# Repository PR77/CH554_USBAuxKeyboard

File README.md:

# CH554 AUX KEYBOARD INTERFACE
USB MACRO PAD (AUX Keyboard Interface) based on the WCH554 MCS51 based chip with USB Device + Host Interface. 

# Warning
This design has not been compliance tested and will not be. It may cause personal damage to you or others. I take no responsibility for this. I accept no responsibility for any damage to any equipment that results from the use of this design and its components. IT IS ENTIRELY AT YOUR OWN RISK!

# Overview
This project is essentially an open source macro pad which emulates a USB Keyboard, Mouse and Comsumer Device. Additionally, there is an OUT USB end point supported to allow for HOST communication back to the device. My target is to make this easily configurable so different functions can be added to the Rotary Encoder, Push Buttons and OLED display. I'm using this project as an opportunity to learn more about the WCH55x micro controller.

# Appearance Final PCB Version
PCB version has been routed manufactured and tested. Gerbers and design now available as it works as expected. Here is the usual 3D artwork of the design.

# Credits
I refacted a lot of the original libraries into various software components. However there were some repos which provided me with excellent information, tools and resources;
- https://github.com/wagiminator
- https://github.com/Blinkinlabs/ch554_sdcc
- https://github.com/HonghongLu/CH554
- https://github.com/pkourany/clickButton

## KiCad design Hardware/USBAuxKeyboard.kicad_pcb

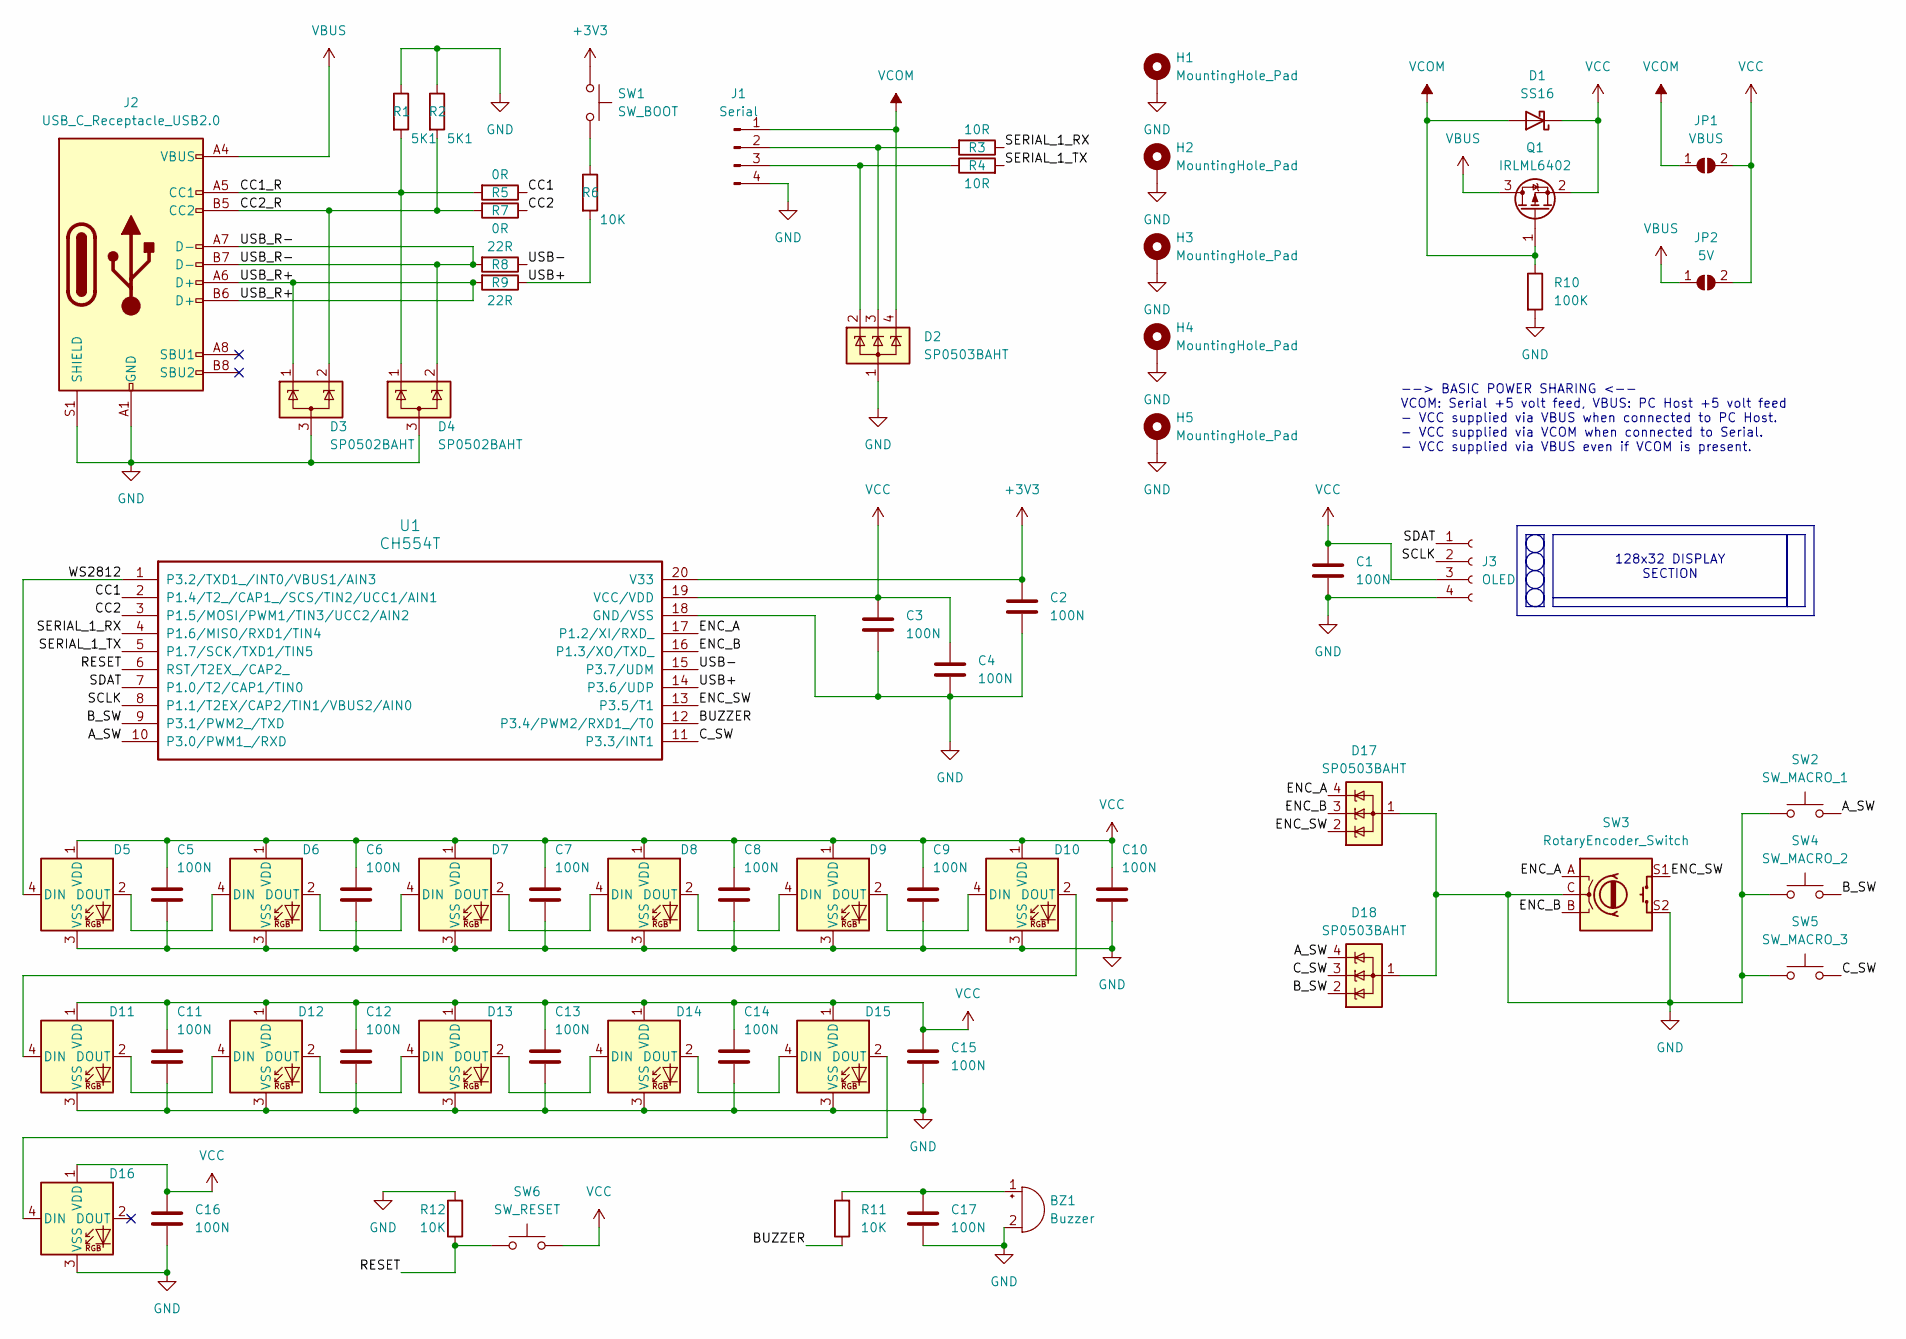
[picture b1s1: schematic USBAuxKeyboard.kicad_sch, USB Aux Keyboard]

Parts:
BZ1: Buzzer; Buzzer_15x7.5RM7.6
C1, C2, C3, C4, C5, C6, C7, C8, C9, C10, C11, C12, C13, C14, C15, C16, C17: 100N; C_0805_2012Metric_Pad1.18x1.45mm_HandSolder
D1: SS16; D_SMA
D2, D17, D18: SP0503BAHT; SOT-143
D3, D4: SP0502BAHT; SOT-23
D5, D6, D7, D8, D9, D10, D11, D12, D13, D14, D15, D16: WS2812B; LED_WS2812B_PLCC4_5.0x5.0mm_P3.2mm
H1, H2, H3, H4, H5: MountingHole_Pad; MountingHole_2.2mm_M2_Pad_Via
J1: Serial; PinHeader_1x04_P2.54mm_Vertical
J2: USB_C_Receptacle_USB2.0; USB_C_Receptacle_HCTL_HC-TYPE-C-16P-01A
J3: OLED; PinSocket_1x04_P2.54mm_Vertical
JP1: VBUS; SolderJumper-2_P1.3mm_Open_RoundedPad1.0x1.5mm
JP2: 5V; SolderJumper-2_P1.3mm_Open_RoundedPad1.0x1.5mm
Q1: IRLML6402; SOT-23
R1, R2: 5K1; R_0805_2012Metric_Pad1.20x1.40mm_HandSolder
R3, R4: 10R; R_0805_2012Metric_Pad1.20x1.40mm_HandSolder
R5, R7: 0R; R_0805_2012Metric_Pad1.20x1.40mm_HandSolder
R6, R11, R12: 10K; R_0805_2012Metric_Pad1.20x1.40mm_HandSolder
R8, R9: 22R; R_0805_2012Metric_Pad1.20x1.40mm_HandSolder
R10: 100K; R_0805_2012Metric_Pad1.20x1.40mm_HandSolder
SW1: SW_BOOT; SW_SPST_B3U-1000P
SW2: SW_MACRO_1; SW_Cherry_MX_1.00u_PCB
SW3: RotaryEncoder_Switch; RotaryEncoder_Alps_EC11E-Switch_Vertical_H20mm
SW4: SW_MACRO_2; SW_Cherry_MX_1.00u_PCB
SW5: SW_MACRO_3; SW_Cherry_MX_1.00u_PCB
SW6: SW_RESET; SW_SPST_B3U-1000P
U1: CH554T; TSSOP-20_4.4x6.5mm_P0.65mm; LCSC C2928938

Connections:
+3V3: C2.1, SW1.2, U1.20 (V33); also elsewhere on the board
/A_SW: D18.4 (K), SW2.1, U1.10 (P3.0/PWM1_/RXD)
/BUZZER: R11.1, U1.12 (P3.4/PWM2/RXD1_/T0)
/B_SW: D18.2 (K), SW4.1, U1.9 (P3.1/PWM2_/TXD)
/CC1: R5.1, U1.2 (P1.4/T2_/CAP1_/SCS/TIN2/UCC1/AIN1)
/CC1_R: D4.1 (K), J2.A5 (CC1), R1.2, R5.2
/CC2: R7.1, U1.3 (P1.5/MOSI/PWM1/TIN3/UCC2/AIN2)
/CC2_R: D3.2 (K), J2.B5 (CC2), R2.2, R7.2
/C_SW: D18.3 (K), SW5.1, U1.11 (P3.3/INT1)
/ENC_A: D17.4 (K), SW3.A, U1.17 (P1.2/XI/RXD_)
/ENC_B: D17.3 (K), SW3.B, U1.16 (P1.3/XO/TXD_)
/ENC_SW: D17.2 (K), SW3.S1, U1.13 (P3.5/T1)
/RESET: R12.1, SW6.1, U1.6 (RST/T2EX_/CAP2_); also elsewhere on the board
/SCLK: J3.2, U1.8 (P1.1/T2EX/CAP2/TIN1/VBUS2/AIN0)
/SDAT: J3.1, U1.7 (P1.0/T2/CAP1/TIN0)
/SERIAL_1_RX: R3.1, U1.4 (P1.6/MISO/RXD1/TIN4)
/SERIAL_1_TX: R4.2, U1.5 (P1.7/SCK/TXD1/TIN5)
/USB+: R6.2, R9.1, U1.14 (P3.6/UDP)
/USB-: R8.1, U1.15 (P3.7/UDM)
/USB_R+: D3.1 (K), J2.A6 (D+), J2.B6 (D+), R9.2
/USB_R-: D4.2 (K), J2.A7 (D-), J2.B7 (D-), R8.2
/WS2812: D5.4 (DIN), U1.1 (P3.2/TXD1_/INT0/VBUS1/AIN3)
GND: BZ1.2 (+), C1.2, C2.2, C3.2, C4.2, C5.2, C6.2, C7.2, C8.2, C9.2, C10.2, C11.2, C12.2, C13.2, C14.2, C15.2, C16.2, C17.2, D2.1 (A), D3.3 (A), D4.3 (A), D5.3 (VSS), D6.3 (VSS), D7.3 (VSS), D8.3 (VSS), D9.3 (VSS), D10.3 (VSS), D11.3 (VSS), D12.3 (VSS), D13.3 (VSS), D14.3 (VSS), D15.3 (VSS), D16.3 (VSS), D17.1 (A), D18.1 (A), H1.1, H2.1, H3.1, H4.1, H5.1, J1.4, J2.A1 (GND), J2.A12 (GND), J2.B1 (GND), J2.B12 (GND), J2.S1 (SHIELD), J3.4, R1.1, R2.1, R10.2, R12.2, SW2.2, SW3.C, SW3.S2, SW4.2, SW5.2, U1.18 (GND/VSS)
unnamed: BZ1.1 (-), C17.1, R11.2
unnamed: D5.2 (DOUT), D6.4 (DIN)
unnamed: D6.2 (DOUT), D7.4 (DIN)
unnamed: D7.2 (DOUT), D8.4 (DIN)
unnamed: D8.2 (DOUT), D9.4 (DIN)
unnamed: D9.2 (DOUT), D10.4 (DIN)
unnamed: D10.2 (DOUT), D11.4 (DIN)
unnamed: D11.2 (DOUT), D12.4 (DIN)
unnamed: D12.2 (DOUT), D13.4 (DIN)
unnamed: D13.2 (DOUT), D14.4 (DIN)
unnamed: D14.2 (DOUT), D15.4 (DIN)
unnamed: D15.2 (DOUT), D16.4 (DIN)
unnamed: D2.3 (K), J1.2, R3.2
unnamed: D2.2 (K), J1.3, R4.1
unnamed 37: R6.1, SW1.1; also elsewhere on the board
VBUS: J2.A4 (VBUS), J2.A9 (VBUS), J2.B4 (VBUS), J2.B9 (VBUS), JP2.1 (A), Q1.3 (D)
VCC: C1.1, C3.1, C4.1, C5.1, C6.1, C7.1, C8.1, C9.1, C10.1, C11.1, C12.1, C13.1, C14.1, C15.1, C16.1, D1.1 (K), D5.1 (VDD), D6.1 (VDD), D7.1 (VDD), D8.1 (VDD), D9.1 (VDD), D10.1 (VDD), D11.1 (VDD), D12.1 (VDD), D13.1 (VDD), D14.1 (VDD), D15.1 (VDD), D16.1 (VDD), J3.3, JP1.2 (B), JP2.2 (B), Q1.2 (S), SW6.2, U1.19 (VCC/VDD); also elsewhere on the board
VCOM: D1.2 (A), D2.4 (K), J1.1, JP1.1 (A), Q1.1 (G), R10.1

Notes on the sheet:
128x32 DISPLAY SECTION
--> BASIC POWER SHARING <-- VCOM: Serial +5 volt feed, VBUS: PC Host +5 volt feed - VCC supplied via VBUS when connected to PC Host. - VCC supplied via VCOM when connected to Serial. - VCC supplied via VBUS even if VCOM is present.

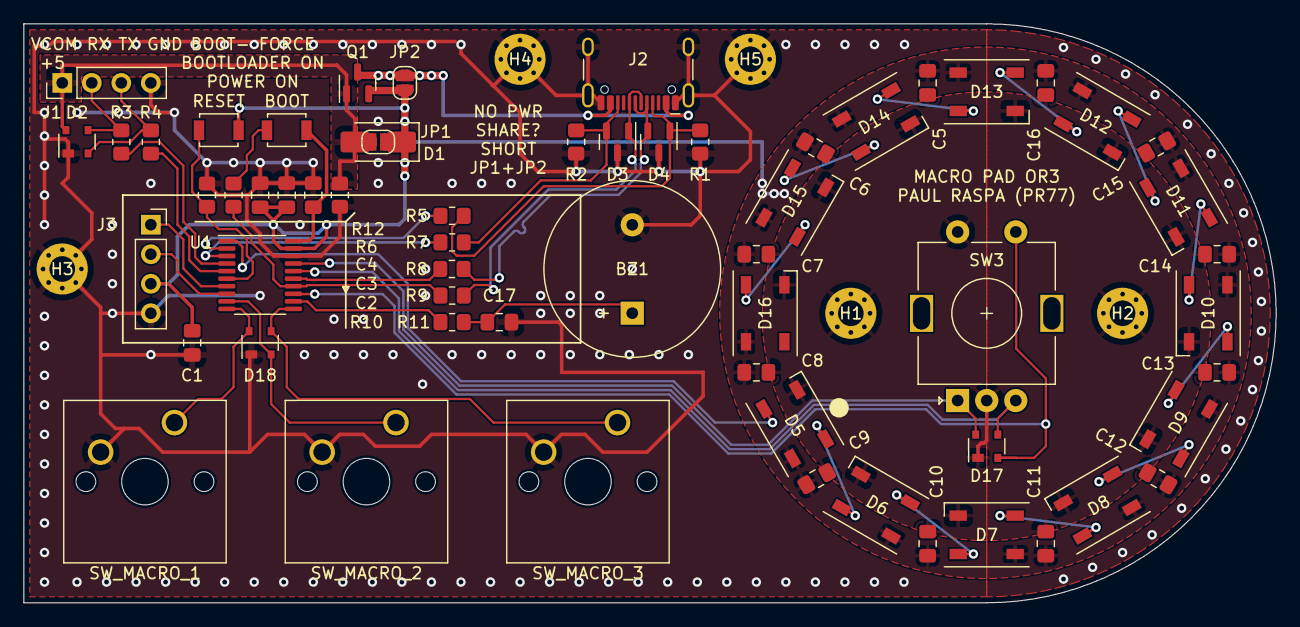
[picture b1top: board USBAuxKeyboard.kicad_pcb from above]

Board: 2 copper layers, 107.7 x 49.8 mm, 66 parts (0 on the bottom side), 41 nets.

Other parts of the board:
BOOT: SW_BOOT; SW_SPST_B3U-1000P
RESET: SW_RESET; SW_SPST_B3U-1000P

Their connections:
+3V3: BOOT.2; also elsewhere on the board
/RESET: RESET.1; also elsewhere on the board
unnamed 37: BOOT.1; also elsewhere on the board
VCC: RESET.2; also elsewhere on the board

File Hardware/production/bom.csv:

Designator,Footprint,Quantity,Value,LCSC Part #
BOOT,SW_SPST_B3U-1000P,1,SW_BOOT,
BZ1,Buzzer_15x7.5RM7.6,1,Buzzer,
"C1, C10, C11, C12, C13, C14, C15, C16, C17, C2, C3, C4, C5, C6, C7, C8, C9",0805,17,100N,
D1,D_SMA,1,SS16,
"D10, D11, D12, D13, D14, D15, D16, D5, D6, D7, D8, D9",LED_WS2812B_PLCC4_5.0x5.0mm_P3.2mm,12,WS2812B,
"D17, D18, D2",SOT-143,3,SP0503BAHT,
"D3, D4",SOT-23,2,SP0502BAHT,
"H1, H2, H3, H4, H5",MountingHole_2.2mm_M2_Pad_Via,5,MountingHole_Pad,
J1,PinHeader_1x04_P2.54mm_Vertical,1,Serial,
J2,USB_C_Receptacle_HCTL_HC-TYPE-C-16P-01A,1,USB_C_Receptacle_USB2.0,
J3,PinSocket_1x04_P2.54mm_Vertical,1,OLED,
JP1,SolderJumper-2_P1.3mm_Open_RoundedPad1.0x1.5mm,1,VBUS,
JP2,SolderJumper-2_P1.3mm_Open_RoundedPad1.0x1.5mm,1,5V,
Q1,SOT-23,1,IRLML6402,
"R1, R2",0805,2,5K1,
R10,0805,1,100K,
"R11, R12, R6",0805,3,10K,
"R3, R4",0805,2,10R,
"R5, R7",0805,2,0R,
"R8, R9",0805,2,22R,
RESET,SW_SPST_B3U-1000P,1,SW_RESET,
SW2,SW_Cherry_MX_1.00u_PCB,1,SW_MACRO_1,
SW3,RotaryEncoder_Alps_EC11E-Switch_Vertical_H20mm,1,RotaryEncoder_Switch,
SW4,SW_Cherry_MX_1.00u_PCB,1,SW_MACRO_2,
SW5,SW_Cherry_MX_1.00u_PCB,1,SW_MACRO_3,
U1,TSSOP-20_4.4x6.5mm_P0.65mm,1,CH554T,C2928938
